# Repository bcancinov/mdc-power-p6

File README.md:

# mdc-power-p6
Modular Detector Controller Power 6V DC-DC Mezzanine Module

## Overview
12V input to 6V output DC-DC module, 3A nominal output, used as one of the `mdc-power-*` bias rails.
Designed for 2 MHz sync operation.
Mezzanine module.

## Power Stage
- Controller: `LT8624S` (`U1`)
  - Silent Switcher 3 synchronous step-down regulator.
  - Ultralow EMI emissions and high efficiency at high switching frequency.
  - Constant-frequency current-mode control.
  - External sync capability.
- Inductor: `L1` = `2.2uH`
  - Uses the XGL4020 shielded power inductor family (see `docs/xgl4020.pdf`).
  - Shielded construction to reduce radiated EMI and coupling into sensitive nodes.
  - Very low DCR family to reduce copper loss and improve efficiency.
  - Low AC loss construction optimized for high-frequency switching.

## Files
- Schematic: `power_p6.pdf`
- Simulation: `sim/` (LTspice and LTpowerCAD files used for loop and transient checks)

## Board Dimensions
- 44.8 mm x 41.5 mm

## Board Stackup
- 4-layer PCB

## CAD
- Designed using KiCad 9.

## Interface
- Control pins: `EN` (enable) and `PG` / `~PGOOD` (power good).
- Connector: `LSHM-140-04.0-L-DV-A-N-K-TR` (Samtec LSHM series) mezzanine for power and control signals.
  - Common pinout is shared across the 16V, -16V, 6V, and 3.3V variants.
  - Unused output rails are tied to GND on the specific module variant.

## Images
Layout:

3D view:

## License

This hardware design is licensed under the **Creative Commons Attribution-NonCommercial-ShareAlike 4.0 International License** (CC BY-NC-SA 4.0).

You are free to download, modify, and build upon this design for your own research or personal use, provided you give appropriate credit and share your modifications under the exact same license. **Commercial manufacturing or use of these designs is strictly prohibited without explicit permission.**

To view a copy of this license, visit [http://creativecommons.org/licenses/by-nc-sa/4.0/](http://creativecommons.org/licenses/by-nc-sa/4.0/) or see the `LICENSE` file in this repository.

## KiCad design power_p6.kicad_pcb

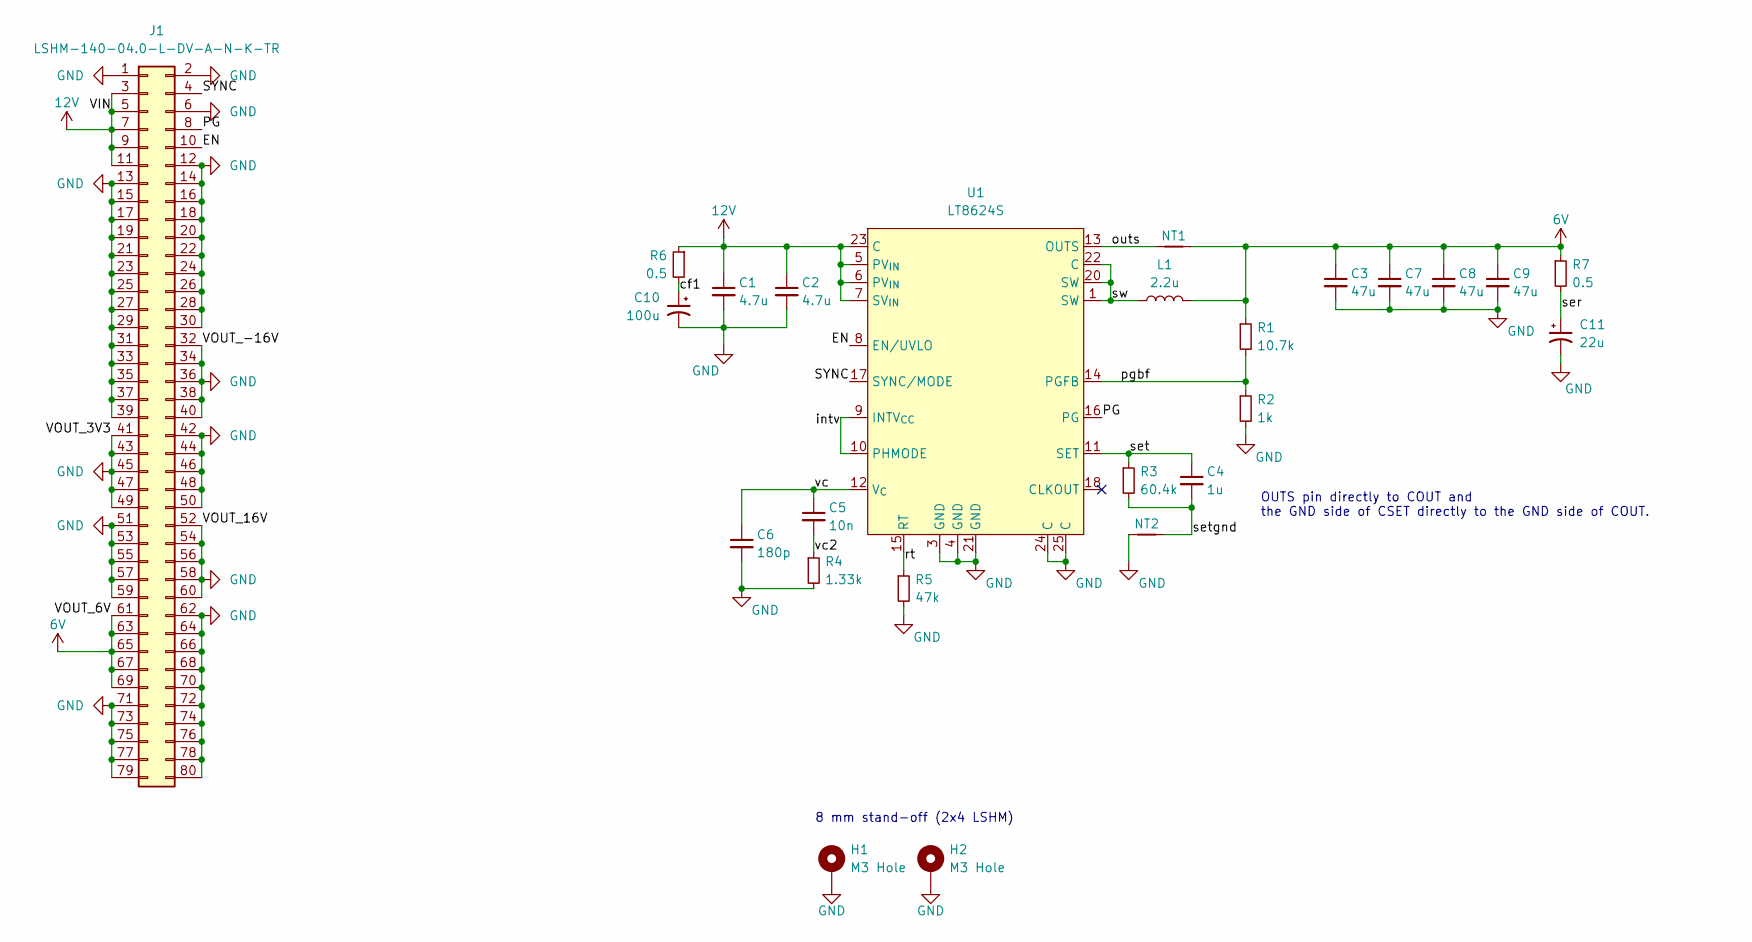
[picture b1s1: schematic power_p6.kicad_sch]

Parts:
C1, C2: 4.7u; C_1210_3225Metric; MPN GCM32ER71H475KA55K
C3, C7, C8, C9: 47u; C_1210_3225Metric; MPN TMK325ABJ476MM-P
C4: 1u; C_0603_1608Metric; MPN GCM188R71E105KA64D
C5: 10n; C_0603_1608Metric; MPN GRT1885C1E103FA02D
C6: 180p; C_0603_1608Metric; MPN GCM1885C2A181FA16J
C10: 100u; T521X; MPN T521X107M025ATE060
C11: 22u; CP_EIA-7343-20_Kemet-V; MPN T521V226M025ATE040
H1, H2: M3 Hole; MountingHole_3.2mm_M3_Pad_Via
J1: LSHM-140-04.0-L-DV-A-N-K-TR; SAMTEC_LSHM-140-04.0-L-DV-A-N-K-TR; MPN LSHM-140-04.0-L-DV-A-N-K-TR
L1: 2.2u; XGL4020; MPN XGL4020-222MEC
NT1, NT2: NetTie_2; NetTie-2_SMD_Pad0.5mm
R1: 10.7k; R_0603_1608Metric; MPN CRCW060310K7FKEA
R2: 1k; R_0603_1608Metric; MPN CRCW06031K00FKEA
R3: 60.4k; R_0603_1608Metric; MPN ERA-3AEB6042V
R4: 1.33k; R_0603_1608Metric; MPN CRCW06031K33FKTA
R5: 47k; R_0603_1608Metric; MPN CRCW060347K0FKEA
R6, R7: 0.5; R_0603_1608Metric; MPN RCWE0603R500FKEA
U1: LT8624S; MPN LT8624SAV#PBF

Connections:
6V: C3.1, C7.1, C8.1, C9.1, J1.61, J1.63, J1.65, J1.67, J1.69, L1.2, NT1.2, R1.1, R7.1
12V: C1.1, C2.1, J1.3, J1.5, J1.7, J1.9, J1.11, R6.1, U1.5 (PV_{IN}), U1.6 (PV_{IN}), U1.7 (SV_{IN}), U1.23 (C)
/EN: J1.10, U1.8 (EN/UVLO)
/PG: J1.8, U1.16 (PG)
/SYNC: J1.4, U1.17 (SYNC/MODE)
/cf1: C10.1, R6.2
/intv: U1.9 (INTV_{CC}), U1.10 (PHMODE)
/outs: NT1.1, U1.13 (OUTS)
/pgbf: R1.2, R2.1, U1.14 (PGFB)
/rt: R5.1, U1.15 (RT)
/ser: C11.1, R7.2
/set: C4.1, R3.1, U1.11 (SET)
/setgnd: C4.2, NT2.2, R3.2
/sw: L1.1, U1.1 (SW), U1.20 (SW), U1.22 (C)
/vc: C5.1, C6.1, U1.12 (V_{C})
/vc2: C5.2, R4.1
GND: C1.2, C2.2, C3.2, C6.2, C7.2, C8.2, C9.2, C10.2, C11.2, H1.1, H2.1, J1.1, J1.2, J1.6, J1.12, J1.13, J1.14, J1.15, J1.16, J1.17, J1.18, J1.19, J1.20, J1.21, J1.22, J1.23, J1.24, J1.25, J1.26, J1.27, J1.28, J1.29, J1.30, J1.31, J1.32, J1.33, J1.34, J1.35, J1.36, J1.37, J1.38, J1.39, J1.40, J1.41, J1.42, J1.43, J1.44, J1.45, J1.46, J1.47, J1.48, J1.49, J1.50, J1.51, J1.52, J1.53, J1.54, J1.55, J1.56, J1.57, J1.58, J1.59, J1.60, J1.62, J1.64, J1.66, J1.68, J1.70, J1.71, J1.72, J1.73, J1.74, J1.75, J1.76, J1.77, J1.78, J1.79, J1.80, NT2.1, R2.2, R4.2, R5.2, U1.3 (GND), U1.4 (GND), U1.21 (GND), U1.24 (C), U1.25 (C)

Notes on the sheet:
OUTS pin directly to COUT and the GND side of CSET directly to the GND side of COUT.
8 mm stand-off (2x4 LSHM)

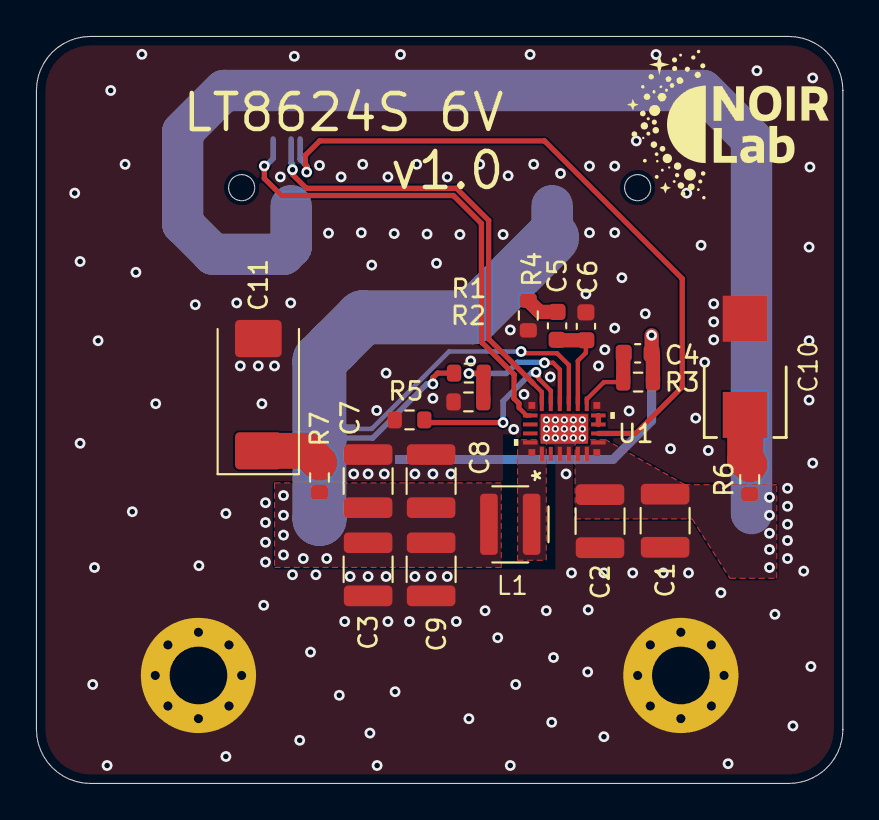
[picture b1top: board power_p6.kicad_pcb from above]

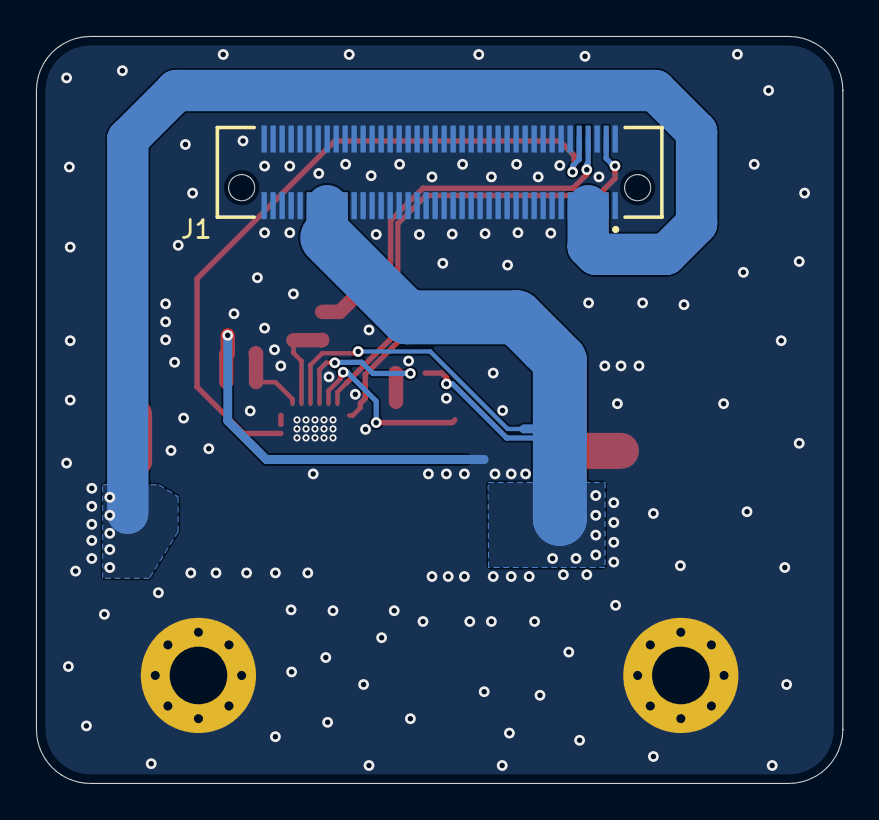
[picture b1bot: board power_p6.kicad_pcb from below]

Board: 4 copper layers, 44.8 x 41.5 mm, 25 parts (3 on the bottom side), 17 nets.

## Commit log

2026-02-06 add pdf
2026-02-06 update readme and docs
2026-02-17 Add input RC snubber
2026-03-18 update set resistor to thin film
2026-03-27 add license
